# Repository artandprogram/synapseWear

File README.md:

# synapseWear

Current release: V1-4
```
$ git clone https://github.com/artandprogram/synapseWear.git
$ cd synapseWear
$ git checkout tags/V1-4
```

If you are interested in hacking and exploring use the master branch.

### iOS

Source for the synapseWear app in the App Store.

### docs

Documentation on the protocols used by the synapseWear device.

### OSX

Allows direct communication between OSX and multiple synapseWear devices. Use of 8 devices simultaneously has been tested. You can save data locally to a file or forward via OSC. 

### Max

Sonification prototyping was done in Max before implementing in Swift (iOS). The Max patches used for prototyping are provided as reference for those interested in using Max with synapseWear.

### firmware

synapseWear firmware for Arduino.

### Server

Over the air updates for synapseWear are downloaded from a server. Server includes an example of that infrastructure for those who want to roll their own code.

### eagle

Eagle files for synapseWear, a 6 layer PCB.

### 3D

synapseWear can also be used as an environmental sensor in your office or home. Use these 3D designs to print your own case.

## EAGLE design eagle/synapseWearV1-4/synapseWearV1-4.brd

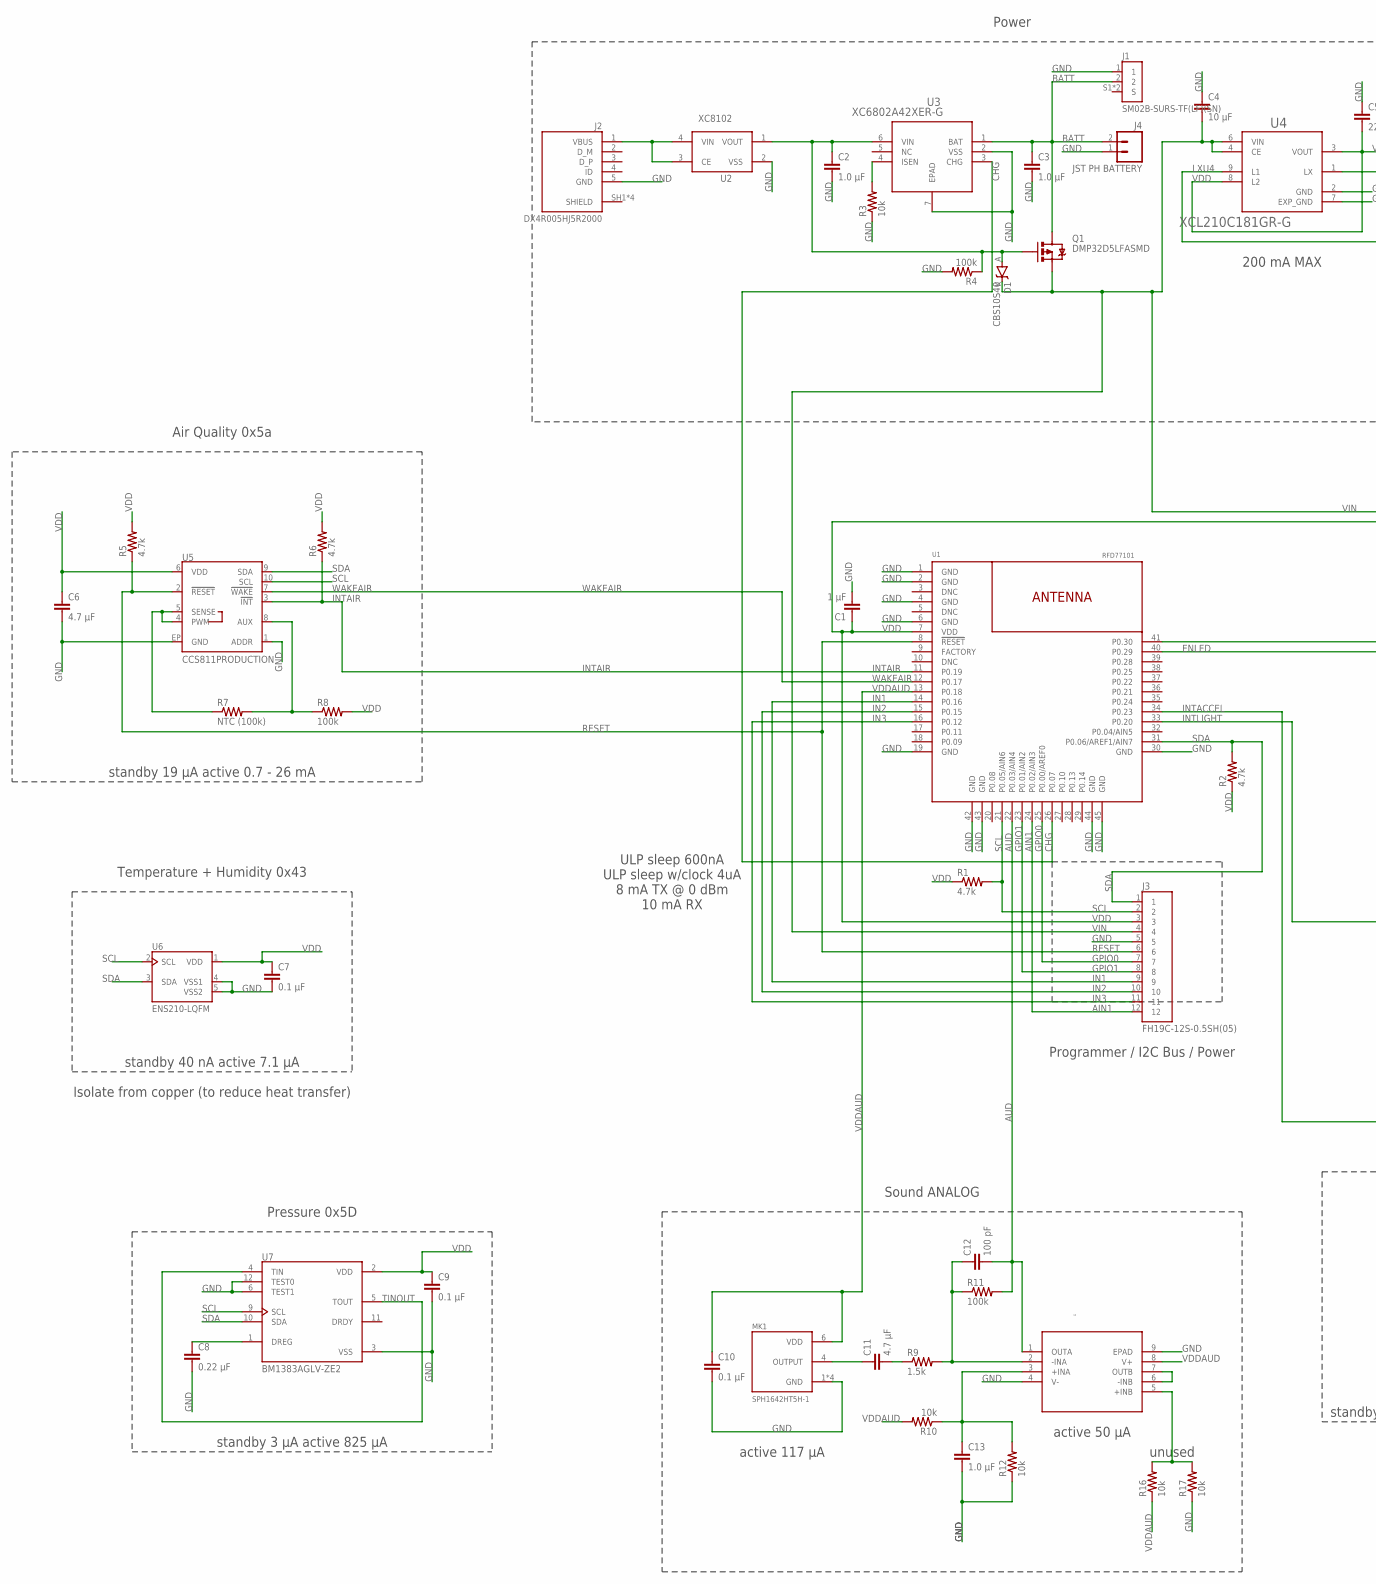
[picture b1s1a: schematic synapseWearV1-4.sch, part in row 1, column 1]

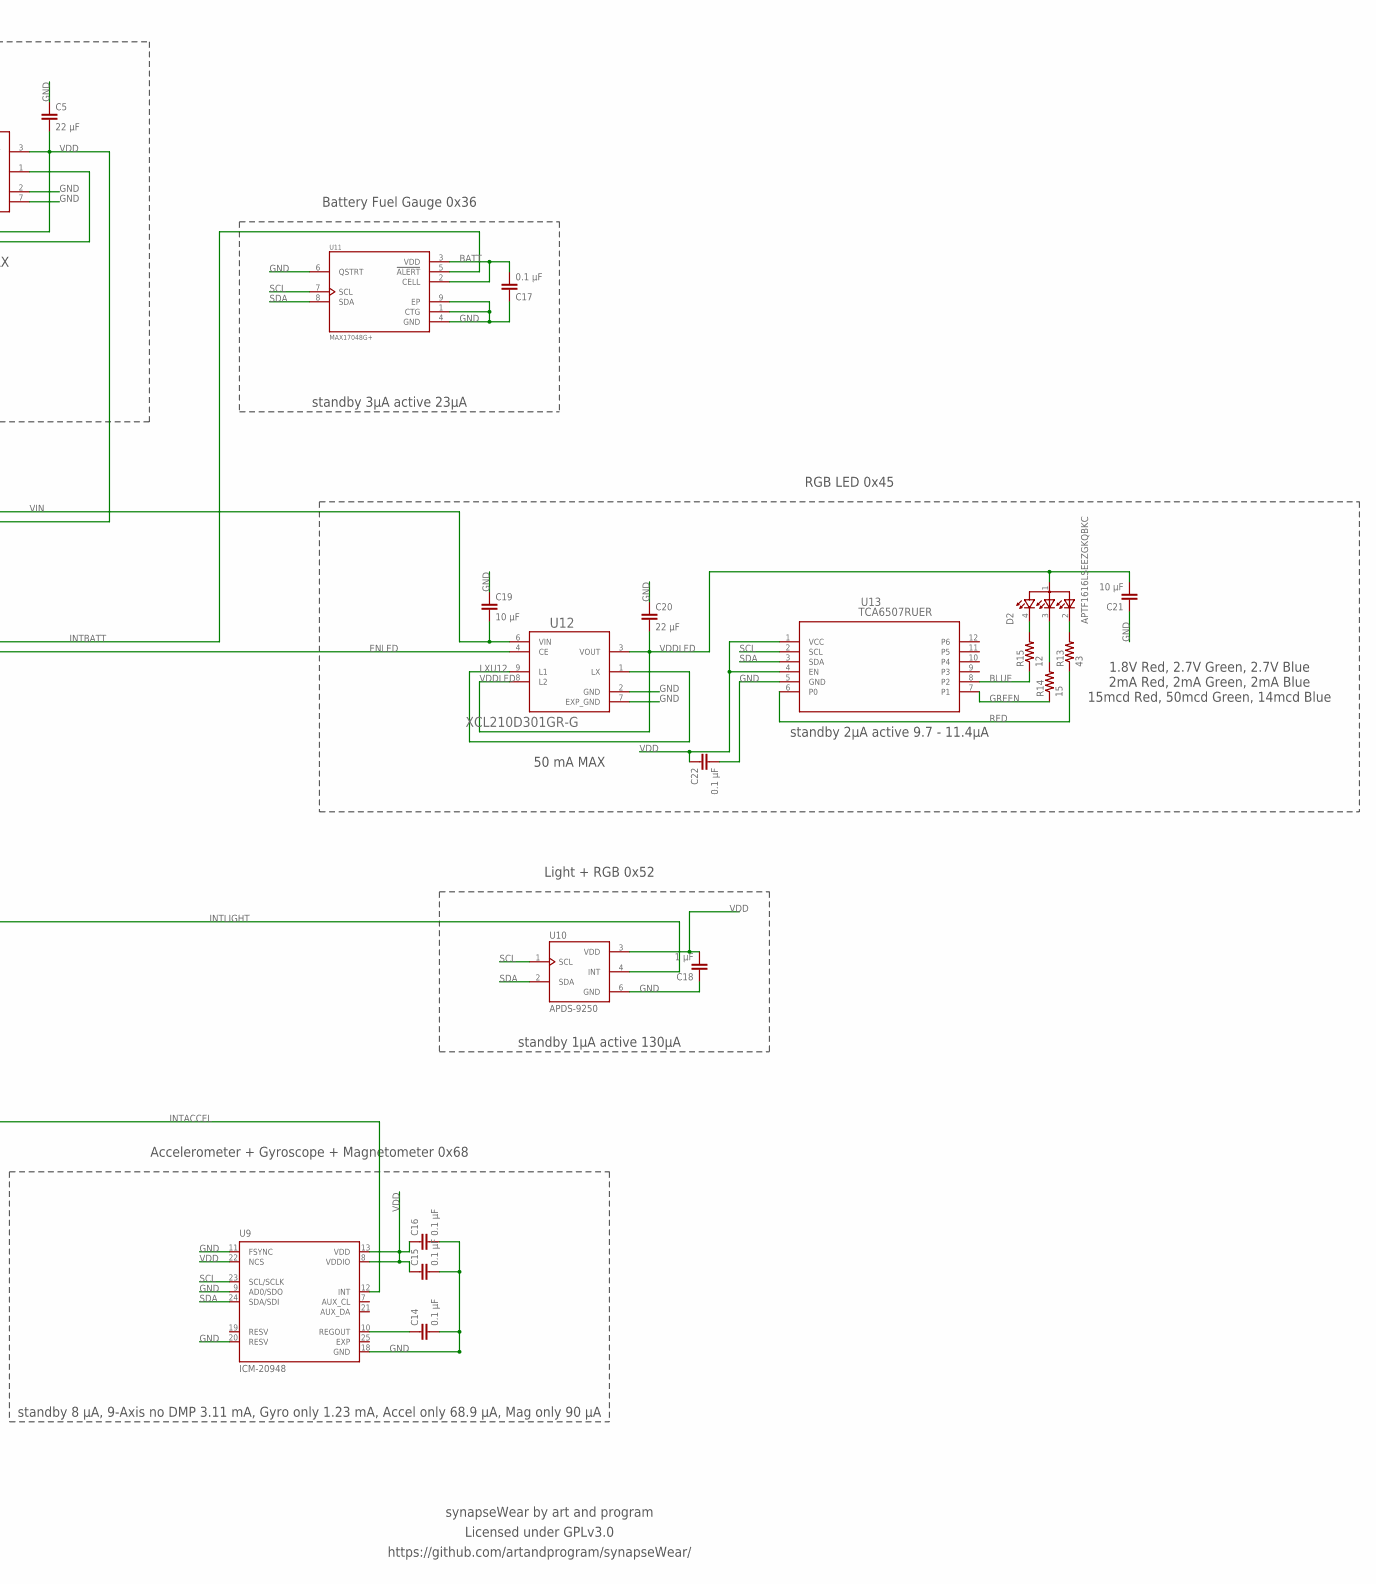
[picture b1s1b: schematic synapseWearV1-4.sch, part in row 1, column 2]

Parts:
C1, C18: 1 μF; 0402-CAP
C2, C3, C13: 1.0 μF; 0402-CAP
C4, C19, C21: 10 μF; 0402-CAP
C5, C20: 22 μF; 0402-CAP
C6, C11: 4.7 μF; 0402-CAP
C7, C9, C10, C14, C15, C16, C17, C22: 0.1 μF; 0402-CAP
C8: 0.22 μF; 0402-CAP
C12: 100 pF; 0402-CAP
D1: CBS10S40; CST2B
D2: APTF1616LSEEZGKQBKC; LEDSC160X160X070-4N
J1: SM02B-SURS-TF(LF)(SN); JST_SM02B-SURS-TF(LF)(SN)
J2: DX4R005HJ5R2000; JAE_DX4R005HJ5R2000
J3: FH19C-12S-0.5SH(05); HRS_FH19C-12S-0.5SH(05)
J4: JST PH BATTERY; JST-2-PTH-VERT
MK1: SPH1642HT5H-1; MIC_SPH1642HT5H-1
Q1: DMP32D5LFASMD; X2-DFN0806-3
R1, R2, R5, R6: 4.7k; 0402-RES
R3, R10, R12, R16, R17: 10k; 0402-RES
R4, R8, R11: 100k; 0402-RES
R7: NTC (100k); 0402-RES
R9: 1.5k; 0402-RES
R13: 43; 0402-RES
R14: 15; 0402-RES
R15: 12; 0402-RES
U1: RFD77101
U2: XC8102; USP-4
U3: XC6802A42XER-G; USP-6C
U4: XCL210C181GR-G; CL-2025-02
U5: CCS811PRODUCTION; LGA10
U6: ENS210-LQFM; SON95P200X200X80-5N160X70
U7: BM1383AGLV-ZE2; PQFN55P250X250X100-12N
U8: OPA2313IDRGT; DRG8_1P2X2P0
U9: ICM-20948; QFN40P300X300X105-25N
U10: APDS-9250; SON65P200X200X75-6N
U11: MAX17048G+; SON50P200X200X80-9N
U12: XCL210D301GR-G; CL-2025-02
U13: TCA6507RUER; RUE12

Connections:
+INA: C13.1, R10.1, R12.2, U8.3 (+INA)
+INB: R16.2, R17.2, U8.5 (+INB)
-INA: C12.1, R9.2, R11.1, U8.2 (-INA)
-INB: U8.6 (-INB), U8.7 (OUTB)
AIN1: J3.12, U1.24 (P0.02/AIN3)
AUD: C12.2, R11.2, U1.22 (P0.03/AIN4), U8.1 (OUTA)
AUX: R7.2, R8.1, U5.8 (AUX)
BATT: C3.1, C17.2, J1.2, J4.2, Q1.D, U3.1 (BAT), U11.2 (CELL), U11.3 (VDD)
BLUE: R15.1, U13.8 (P2)
CHG: U1.26 (P0.07), U3.3 (CHG)
DREG: C8.1, U7.1 (DREG)
ENLED: U1.40 (P0.29), U12.4 (CE)
GND: C1.2, C2.2, C3.2, C4.1, C5.1, C6.2, C7.2, C8.2, C9.2, C10.2, C13.2, C14.2, C15.2, C16.2, C17.1, C18.1, C19.1, C20.1, C21.1, C22.2, J1.1, J2.5 (GND), J3.5, J4.1, MK1.1 (GND), MK1.2 (GND), MK1.3 (GND), MK1.5 (GND), R3.1, R4.2, R12.1, R17.1, U1.1 (GND), U1.2 (GND), U1.4 (GND), U1.6 (GND), U1.19 (GND), U1.30 (GND), U1.42 (GND), U1.43 (GND), U1.44 (GND), U1.45 (GND), U2.2 (VSS), U3.2 (VSS), U3.7 (EPAD), U4.2 (GND), U4.7 (EXP_GND), U5.1 (ADDR), U5.EP (GND), U6.4 (VSS1), U6.5 (VSS2), U7.3 (VSS), U7.6 (TEST1), U7.12 (TEST0), U8.4 (V-), U8.9 (EPAD), U9.9 (AD0/SDO), U9.11 (FSYNC), U9.18 (GND), U9.20 (RESV), U10.6 (GND), U11.1 (CTG), U11.4 (GND), U11.6 (QSTRT), U11.9 (EP), U12.2 (GND), U12.7 (EXP_GND), U13.5 (GND)
GPIO0: J3.7, U1.25 (P0.00/AREF0)
GPIO1: J3.8, U1.23 (P0.01/AIN2)
GREEN: R14.1, U13.7 (P1)
IN1: J3.9, U1.14 (P0.16)
IN2: J3.10, U1.15 (P0.15)
IN3: J3.11, U1.16 (P0.12)
INTACCEL: U1.34 (P0.23), U9.12 (INT)
INTAIR: R6.1, U1.11 (P0.19), U5.3 (!INT!)
INTBATT: U1.41 (P0.30), U11.5 (!ALERT)
INTLIGHT: U1.33 (P0.20), U10.4 (INT)
ISEN: R3.2, U3.4 (ISEN)
LEDBRES: D2.4, R15.2
LEDGRES: D2.3, R14.2
LEDRRES: D2.2, R13.2
LXU4: U4.1 (LX), U4.9 (L1)
LXU12: U12.1 (LX), U12.9 (L1)
MKOUT1: C11.1, MK1.4 (OUTPUT)
MKOUT2: C11.2, R9.1
NTC_SENSE: R7.1, U5.4 (PWM), U5.5 (SENSE)
RED: R13.1, U13.6 (P0)
REGOUT: C14.1, U9.10 (REGOUT)
RESET: J3.6, R5.1, U1.8 (!RESET!), U5.2 (!RESET!)
SCL: J3.2, R1.2, U1.21 (P0.05/AIN6), U5.10 (SCL), U6.2 (SCL), U7.9 (SCL), U9.23 (SCL/SCLK), U10.1 (SCL), U11.7 (SCL), U13.2 (SCL)
SDA: J3.1, R2.2, U1.31 (P0.06/AREF1/AIN7), U5.9 (SDA), U6.3 (SDA), U7.10 (SDA), U9.24 (SDA/SDI), U10.2 (SDA), U11.8 (SDA), U13.3 (SDA)
TINOUT: U7.4 (TIN), U7.5 (TOUT)
VBUS: C2.1, D1.A, Q1.G, R4.1, U2.1 (VOUT), U3.6 (VIN)
VCCUSB: J2.1 (VBUS), U2.3 (CE), U2.4 (VIN)
VDD: C1.1, C5.2, C6.1, C7.1, C9.1, C15.1, C16.1, C18.2, C22.1, J3.3, R1.1, R2.1, R5.2, R6.2, R8.2, U1.7 (VDD), U4.3 (VOUT), U4.8 (L2), U5.6 (VDD), U6.1 (VDD), U7.2 (VDD), U9.8 (VDDIO), U9.13 (VDD), U9.22 (NCS), U10.3 (VDD), U13.1 (VCC), U13.4 (EN)
VDDAUD: C10.1, MK1.6 (VDD), R10.2, R16.1, U1.13 (P0.18), U8.8 (V+)
VDDLED: C20.2, C21.2, D2.1, U12.3 (VOUT), U12.8 (L2)
VIN: C4.2, C19.2, D1.K, J3.4, Q1.S, U4.4 (CE), U4.6 (VIN), U12.6 (VIN)
WAKEAIR: U1.12 (P0.17), U5.7 (!WAKE!)

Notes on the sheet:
Air Quality 0x5a
Power
Temperature + Humidity 0x43
Isolate from copper (to reduce heat transfer)
Pressure 0x5D
Sound ANALOG
Accelerometer + Gyroscope + Magnetometer 0x68
Programmer / I2C Bus / Power
synapseWear by art and program
Licensed under GPLv3.0
Battery Fuel Gauge 0x36
Light + RGB 0x52
standby 2μA active 9.7 - 11.4μA
1.8V Red, 2.7V Green, 2.7V Blue 2mA Red, 2mA Green, 2mA Blue 15mcd Red, 50mcd Green, 14mcd Blue
standby 19 μA active 0.7 - 26 mA
standby 40 nA active 7.1 μA
standby 3 μA active 825 μA
active 117 μA
active 50 μA
standby 8 μA, 9-Axis no DMP 3.11 mA, Gyro only 1.23 mA, Accel only 68.9 μA, Mag only 90 μA
standby 1μA active 130μA
standby 3μA active 23μA
200 mA MAX
50 mA MAX
unused
RGB LED 0x45
ULP sleep 600nA ULP sleep w/clock 4uA 8 mA TX @ 0 dBm 10 mA RX
https://github.com/artandprogram/synapseWear/

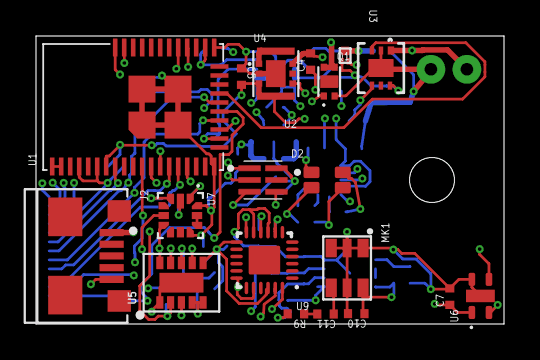
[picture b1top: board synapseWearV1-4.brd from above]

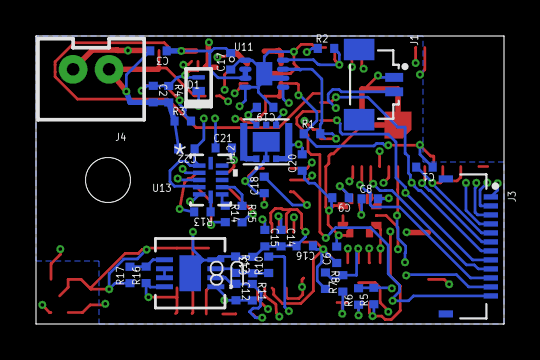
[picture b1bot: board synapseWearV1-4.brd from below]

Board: 6 copper layers, 26.0 x 16.0 mm, 60 parts (41 on the bottom side), 45 nets.

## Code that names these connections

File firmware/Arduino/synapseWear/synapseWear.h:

/*
  Library for synapseWear
  Created by Alexander Reeder, 2017 Apr 1
  For license and other information refer to https://github.com/artandprogram/synapseWear
*/

#ifndef _SYNAPSEWEAR_H
#define _SYNAPSEWEAR_H

#include "APDS9250.h"
#include "BM1383AGLV.h"
#include "LPS25H.h"
#include "CCS811.h"
#include "ENS210.h"
#include "ICM20948.h"
#include "MAX17048.h"
#include "SPH1642HT5H.h"
#include "TCA6507.h"

#define FIRMWARE_VERSION_MAJOR 1
#define FIRMWARE_VERSION_MINOR 3
#define FIRMWARE_DATE 20200208

#define PIN_AUD       3
#define PIN_BATTCHG   7
#define PIN_WAKEAIR   17
#define PIN_VDDAUD    18
#define PIN_INTAIR    19
#define PIN_VDDLIGHT  20
#define PIN_INTACCEL  23
#define PIN_ENLED     29
#define PIN_INTBATT   30

#define MODE_NORMAL     0x00
#define MODE_LIVE       0x01
#define MODE_LOWPOWER   0x02


#define SYNAPSEWEAR_SETTINGS_FLASH  230 // 240 - 251 used by ota_bootloader
#define SYNAPSEWEAR_INITIALIZED_VALUE 12345678
#define DEFAULT_INTERVAL 60000
#define SENSOROFF_DELAY 30000

class SYNAPSEWEAR {

  public:

    void begin();
    void pingI2C();
    void update();
    void setInterval(uint32_t);
    void bleOnConnect();
    void bleOnDisconnect();
    void bleOnReceive(char *, int);
    void beginCharging();
    void endCharging();

    APDS9250 apds9250 = APDS9250();
    BM1383AGLV bm1383aglv = BM1383AGLV();
    LPS25H lps25h = LPS25H();
    CCS811 ccs811 = CCS811(PIN_WAKEAIR);
    ENS210 ens210 = ENS210();
    ICM20948 icm20948 = ICM20948();
    MAX17048 max17048 = MAX17048();
    SPH1642HT5H sph1642ht5h = SPH1642HT5H(PIN_VDDAUD, PIN_AUD);
    TCA6507 tca6507 = TCA6507(PIN_ENLED, PIN_BATTCHG);

  private:

    void bleUpdate();
    void bleDataPrep();
    void bleDataDone();
    void bleDataCopy(uint8_t *, uint8_t);
    void bleDataUint8(uint8_t);
    void bleDataUint16(uint16_t);
    void bleDataFloatUint8(float);
    void bleDataFloatUint16(float);
    void bleShowData();
    void saveFirmwareSettings();
    bool validateAccessKey(char *, uint8_t);
    void enableSensors();
    void disableSensors();

    char *deviceName = "synapse";
    struct synapseWearSettings_t
    {
      uint32_t initialized;
      char accessKey[8];
      bool deviceAssociated;
      uint32_t interval;
      uint8_t mode;
      bool co2Enabled;
      bool tempEnabled;
      bool humidityEnabled;
      bool lightEnabled;
      bool pressureEnabled;
      bool soundEnabled;
      bool accelEnabled;
      bool gyroEnabled;
      bool ledEnabled;
    };

    struct synapseWearSettings_t settings;
    uint32_t nextUpdate = 0;
    uint32_t interval = DEFAULT_INTERVAL;
    char sendBuf[256] = {0};
    uint8_t sendBufCount = 0;
    uint8_t sendBufOffset = 0;
    uint8_t sendBufToSend = 0;
    uint8_t sendBufSendCount = 0;
    bool bleSetup = false;
    bool bleConnected = false;
    bool dataReady = false;
    bool timeToSleep = false;
    bool bleAuthenticated = false;
    bool disableSensorsCountdown = false;
    uint32_t dataFrame = 0;
    uint32_t dataLastSentTime = 0;
    uint8_t lastBleCommandReceived = 0;
    uint32_t dataPrepStartTime = 0;
    uint32_t disableSensorsTime = 0;
    synapseWearSettings_t *p = (synapseWearSettings_t*)ADDRESS_OF_PAGE(SYNAPSEWEAR_SETTINGS_FLASH);

};

#endif

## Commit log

2018-09-27 Adding directory structure
2018-09-27 add synapseWear source to iOS
2018-09-27 add synapseWearCentral source to OSX
2018-09-27 modify synapsewear app setting
2018-09-27 building notes
2018-09-27 synapseWear firmware
2018-09-27 eagle pcb design for Kickstarter version
2018-09-27 remove .DS_Store
2018-09-29 OTA server infrastructure
2018-09-29 Max project used for prototyping synapseWear sonification
2018-09-29 3D printable wall enclosure for synapseWear
2018-10-04 Filling out LPS25H support
2018-10-04 update FIRMWARE_DATE
2018-10-06 Adding synapsWear protocol and data format
2018-10-07 Documenting
2018-11-29 Add Today Extension
2019-02-04 Updated synapseWearData.txt, various cleaning, preparing for next iOS app release
2019-02-10 Adding 0.05s (20hz) timing Time should be sent via OSC with millis but there is a problem in both OS X and iOS app (library bug?), so: - added timeSec - added timeMillis to OSC data Also added UUID f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
2019-04-13 modifying debug output, fix mistake in docs
2019-05-29 make some fixes
2019-05-29 Add Android initial version
2019-06-04 Bug fix to Android toSynapseInt
2019-06-07 make some fixes in OSX
2019-06-08 Fixed uploading data array in background
2019-06-10 Fix in sending values array to service
2019-06-10 Refactor code
2019-06-10 Fix in sending array after specified time
2019-07-09 modify export file function
2019-07-24 add realtime graph and flash led
2019-07-31 modify graph length setting
2019-08-13 add graph view
2019-08-15 modify Today Extension
2019-08-23 modify realtime graph
2019-08-29 add realtime graph setting (0.2 sec) and bug fix
2019-09-04 make some fixes in iOS
2019-09-20 modify design in analyze page
2019-09-26 replace to new icon and correspond to iOS13
2019-10-01 add acceleration graph and add graph hidden function
2019-10-30 add debug page
2019-11-25 add data management function
2019-11-28 open multiple windows and modify the graph to update in realtime
2019-12-17 add firmwear update function
2019-12-24 modify DFU function
2020-01-14 modify memory leak
2020-01-17 modify setting information
2020-01-24 modify to reuse UITableViewCell
2020-01-31 modify FileManager functions
2020-02-04 add device reboot function
2020-02-08 synapseWear iOS 1.6 release
2020-02-10 bug fix
2020-02-11 1.7 release for firmware update Reset support in firmware
2021-01-11 Bump redcarpet
    Bumps [redcarpet](https://github.com/vmg/redcarpet) from 3.4.0 to 3.5.1.
    - [Release notes](https://github.com/vmg/redcarpet/releases)
    - [Changelog](https://github.com/vmg/redcarpet/blob/master/CHANGELOG.md)
    - [Commits](https://github.com/vmg/redcarpet/compare/v3.4.0...v3.5.1)
2021-02-01 add save process to local file
2021-02-04 change the data save destination from the Documents folder to the Application Support folder
2022-04-05 Bump cocoapods-downloader
    Bumps [cocoapods-downloader](https://github.com/CocoaPods/cocoapods-downloader) from 1.2.1 to 1.6.3.
    - [Release notes](https://github.com/CocoaPods/cocoapods-downloader/releases)
    - [Changelog](https://github.com/CocoaPods/cocoapods-downloader/blob/master/CHANGELOG.md)
    - [Commits](https://github.com/CocoaPods/cocoapods-downloader/compare/1.2.1...1.6.3)
    ---
    updated-dependencies:
2022-07-22 Bump tzinfo
    Bumps [tzinfo](https://github.com/tzinfo/tzinfo) from 1.2.5 to 1.2.10.
    - [Release notes](https://github.com/tzinfo/tzinfo/releases)
    - [Changelog](https://github.com/tzinfo/tzinfo/blob/master/CHANGES.md)
    - [Commits](https://github.com/tzinfo/tzinfo/compare/v1.2.5...v1.2.10)
    ---
    updated-dependencies:

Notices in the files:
parts and their libraries:
synapseWearV2: Licensing: GPL v3.0 - https://www.gnu.org/licenses/gpl-3.0.en.html
synapseWearV2: © 2015 RF Digital Corporation
SparkFun-Connectors: Licensing: Creative Commons ShareAlike 4.0 International - https://creativecommons.org/licenses/by-sa/4.0
